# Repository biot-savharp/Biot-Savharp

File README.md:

# Biot-Savharp

Directory of folders/files in this repository
- ATTiny: Arduino code running on ATTiny45s (generating square waves sent to electromagnets to actuate strings)
- ArduinoISP: Arduino code to use an Arduino as an ISP to program ATTiny45s. This code is identical to the one found in the official Arduino Examples and requires some tweaking depending on what master Arduino is being used, etc.
- Datasheets: datasheets for the various chips used in the electromagnet driver board (AND gates, driver, and MOSFET)
- EM Harp: Eagle PCB layout files for the electromagnet driver board (.brd for board, .dru for design rules, .sch for schematic, and .epf for eagle project file)
- Keyboard: Arduino code running on an Arduino MEGA getting inputs from the keyboard and transmitting on/off signals for each key to the electromagnet driver board
- Keyboard_Laser: DWG file for laser-cutting the wooden keys of the keyboard
- MEGA Shield: Arduino MEGA breakout board interfacing with the keyboard and with connectors to the electromagnet driver board
- Notebook.pdf: my design notebook! The authoritative source of documentation, and a record of all the failures that led to eventual success
- harp_string_lengths.xlsx: an excel spreadsheet for calculating string lengths depending on tension

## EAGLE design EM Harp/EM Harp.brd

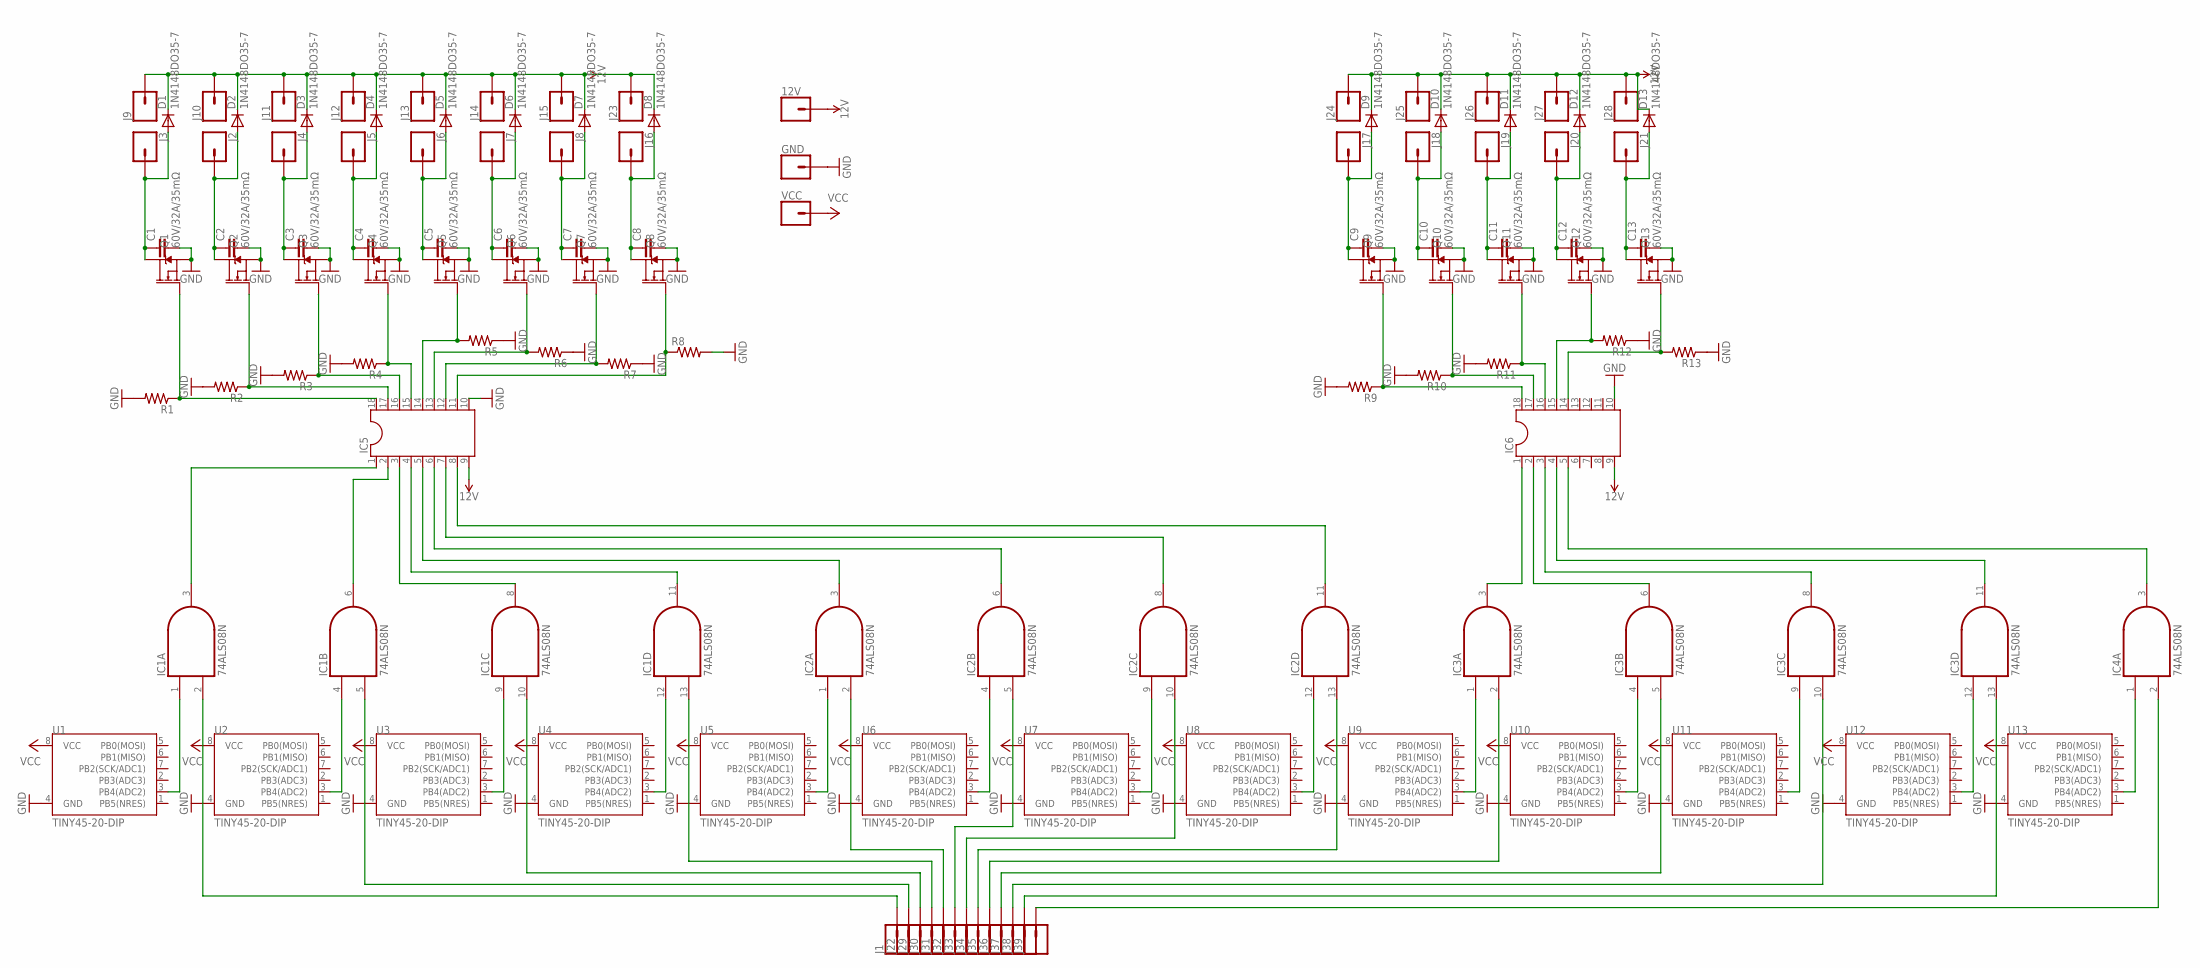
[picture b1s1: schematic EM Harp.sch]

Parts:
12V: CONN_01; 1X01
C1, C2, C3, C4, C5, C6, C7, C8, C9, C10, C11, C12, C13: C; C0805
D1, D2, D3, D4, D5, D6, D7, D8, D9, D10, D11, D12, D13: 1N4148DO35-7; DO35-7
GND: CONN_01; 1X01
IC1, IC2, IC3, IC4: 74ALS08N; DIL14
IC5, IC6: DIL18
J1, J2, J3, J4, J5, J6, J7, J8, J9, J10, J11, J12, J13, J14, J15, J16, J17, J18, J19, J20, J21, J22, J23, J24, J25, J26, J27, J28, J29, J30, J31, J32, J33, J34, J35, J36, J37, J38, J39: CONN_01; 1X01
Q1, Q2, Q3, Q4, Q5, Q6, Q7, Q8, Q9, Q10, Q11, Q12, Q13: 60V/32A/35mΩ; TO220V
R1: R-US_M0805; M0805
R2, R3, R4, R5, R6, R7, R8, R9, R10, R11, R12, R13: R-US_R0805; R0805
U1, U2, U3, U4, U5, U6, U7, U8, U9, U10, U11, U12, U13: TINY45-20-DIP; DIP08_MCU
VCC: CONN_01; 1X01

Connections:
12V: 12V.1, D1.C, D2.C, D3.C, D4.C, D5.C, D6.C, D7.C, D8.C, D9.C, D10.C, D11.C, D12.C, D13.C, IC5.9, IC6.9, J9.1, J10.1, J11.1, J12.1, J13.1, J14.1, J15.1, J23.1, J24.1, J25.1, J26.1, J27.1, J28.1
GND: C1.2, C2.2, C3.2, C4.2, C5.2, C6.2, C7.2, C8.2, C9.2, C10.2, C11.2, C12.2, C13.2, GND.1, IC1.7 (GND), IC2.7 (GND), IC3.7 (GND), IC4.7 (GND), IC5.10, IC6.10, Q1.3 (S), Q2.3 (S), Q3.3 (S), Q4.3 (S), Q5.3 (S), Q6.3 (S), Q7.3 (S), Q8.3 (S), Q9.3 (S), Q10.3 (S), Q11.3 (S), Q12.3 (S), Q13.3 (S), R1.2, R2.2, R3.2, R4.2, R5.1, R6.1, R7.1, R8.2, R9.2, R10.2, R11.2, R12.1, R13.1, U1.4 (GND), U2.4 (GND), U3.4 (GND), U4.4 (GND), U5.4 (GND), U6.4 (GND), U7.4 (GND), U8.4 (GND), U9.4 (GND), U10.4 (GND), U11.4 (GND), U12.4 (GND), U13.4 (GND)
unnamed: IC1.1 (I0), U1.3 (PB4(ADC2))
unnamed: IC1.4 (I0), U2.3 (PB4(ADC2))
unnamed: IC1.9 (I0), U3.3 (PB4(ADC2))
unnamed: IC1.12 (I0), U4.3 (PB4(ADC2))
unnamed: IC2.1 (I0), U5.3 (PB4(ADC2))
unnamed: IC2.4 (I0), U6.3 (PB4(ADC2))
unnamed: IC2.9 (I0), U7.3 (PB4(ADC2))
unnamed: IC2.12 (I0), U8.3 (PB4(ADC2))
unnamed: IC3.1 (I0), U9.3 (PB4(ADC2))
unnamed: IC3.4 (I0), U10.3 (PB4(ADC2))
unnamed: IC3.9 (I0), U11.3 (PB4(ADC2))
unnamed: IC3.12 (I0), U12.3 (PB4(ADC2))
unnamed: IC4.1 (I0), U13.3 (PB4(ADC2))
unnamed: IC1.2 (I1), J1.1
unnamed: IC1.5 (I1), J22.1
unnamed: IC1.10 (I1), J29.1
unnamed: IC1.13 (I1), J30.1
unnamed: IC2.2 (I1), J31.1
unnamed: IC2.5 (I1), J32.1
unnamed: IC2.10 (I1), J33.1
unnamed: IC2.13 (I1), J34.1
unnamed: IC3.2 (I1), J35.1
unnamed: IC3.5 (I1), J36.1
unnamed: IC3.10 (I1), J37.1
unnamed: IC3.13 (I1), J38.1
unnamed: IC4.2 (I1), J39.1
unnamed: IC1.3 (O), IC5.1
unnamed: IC1.6 (O), IC5.2
unnamed: IC1.8 (O), IC5.3
unnamed: IC1.11 (O), IC5.4
unnamed: IC2.3 (O), IC5.5
unnamed: IC2.6 (O), IC5.6
unnamed: IC2.8 (O), IC5.7
unnamed: IC2.11 (O), IC5.8
unnamed: IC3.3 (O), IC6.1
unnamed: IC3.6 (O), IC6.2
unnamed: IC3.8 (O), IC6.3
unnamed: IC3.11 (O), IC6.4
unnamed: IC4.3 (O), IC6.5
unnamed: IC5.18, Q1.1 (G), R1.1
unnamed: IC5.17, Q2.1 (G), R2.1
unnamed: IC5.16, Q3.1 (G), R3.1
unnamed: IC5.15, Q4.1 (G), R4.1
unnamed: IC5.14, Q5.1 (G), R5.2
unnamed: IC5.13, Q6.1 (G), R6.2
unnamed: IC5.12, Q7.1 (G), R7.2
unnamed: C1.1, D1.A, J3.1, Q1.2 (D)
unnamed: IC6.18, Q9.1 (G), R9.1
unnamed: IC6.17, Q10.1 (G), R10.1
unnamed: IC6.16, Q11.1 (G), R11.1
unnamed: IC6.15, Q12.1 (G), R12.2
unnamed: IC6.14, Q13.1 (G), R13.2
unnamed: C7.1, D7.A, J8.1, Q7.2 (D)
unnamed: C6.1, D6.A, J7.1, Q6.2 (D)
unnamed: C5.1, D5.A, J6.1, Q5.2 (D)
unnamed: C4.1, D4.A, J5.1, Q4.2 (D)
unnamed: C3.1, D3.A, J4.1, Q3.2 (D)
unnamed: C2.1, D2.A, J2.1, Q2.2 (D)
unnamed: C8.1, D8.A, J16.1, Q8.2 (D)
unnamed: C13.1, D13.A, J21.1, Q13.2 (D)
unnamed: C12.1, D12.A, J20.1, Q12.2 (D)
unnamed: C11.1, D11.A, J19.1, Q11.2 (D)
unnamed: C10.1, D10.A, J18.1, Q10.2 (D)
unnamed: C9.1, D9.A, J17.1, Q9.2 (D)
unnamed: IC5.11, Q8.1 (G), R8.1
VCC: IC1.14 (VCC), IC2.14 (VCC), IC3.14 (VCC), IC4.14 (VCC), U1.8 (VCC), U2.8 (VCC), U3.8 (VCC), U4.8 (VCC), U5.8 (VCC), U6.8 (VCC), U7.8 (VCC), U8.8 (VCC), U9.8 (VCC), U10.8 (VCC), U11.8 (VCC), U12.8 (VCC), U13.8 (VCC), VCC.1

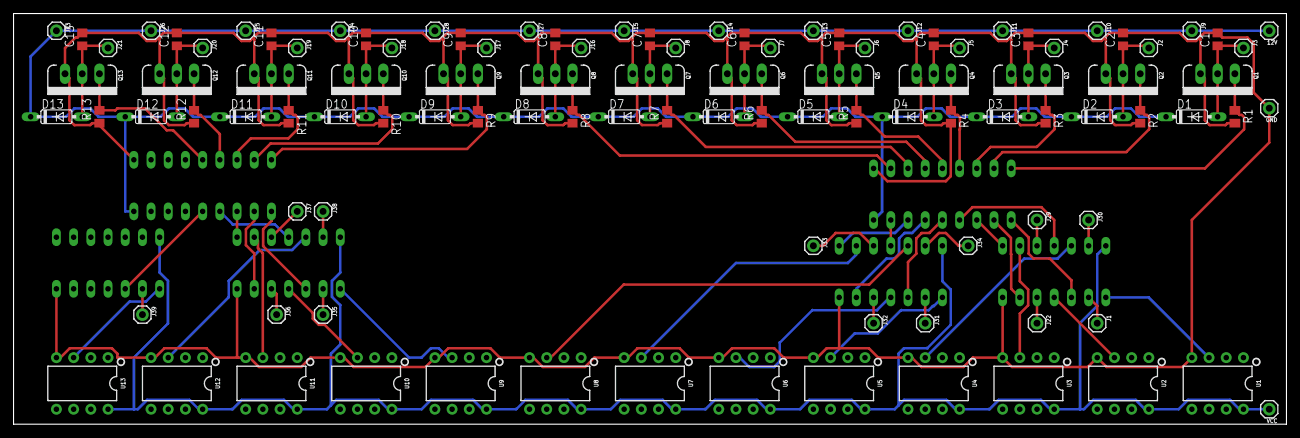
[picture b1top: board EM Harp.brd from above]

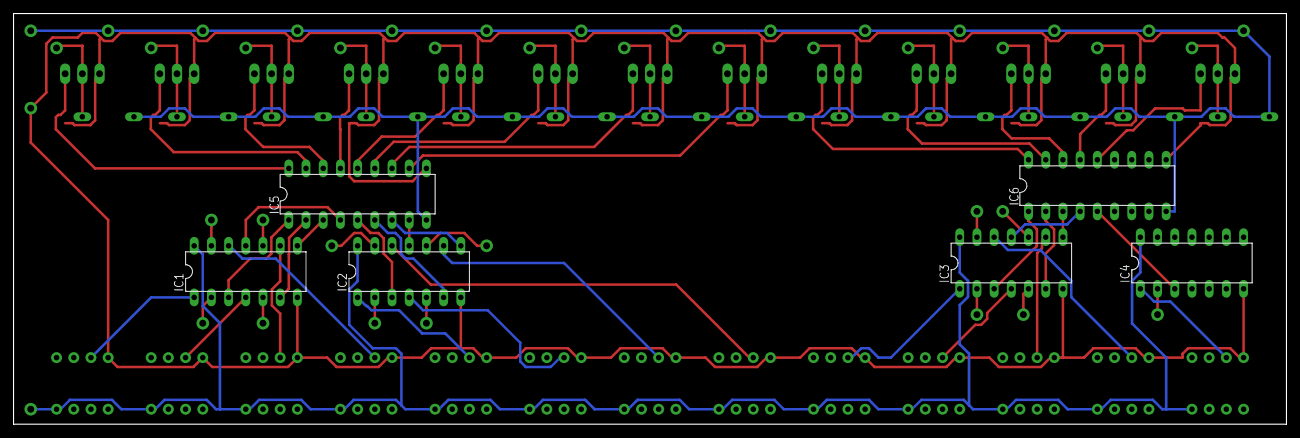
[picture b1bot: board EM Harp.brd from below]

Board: 2 copper layers, 187.9 x 60.6 mm, 113 parts (6 on the bottom side), 68 nets.

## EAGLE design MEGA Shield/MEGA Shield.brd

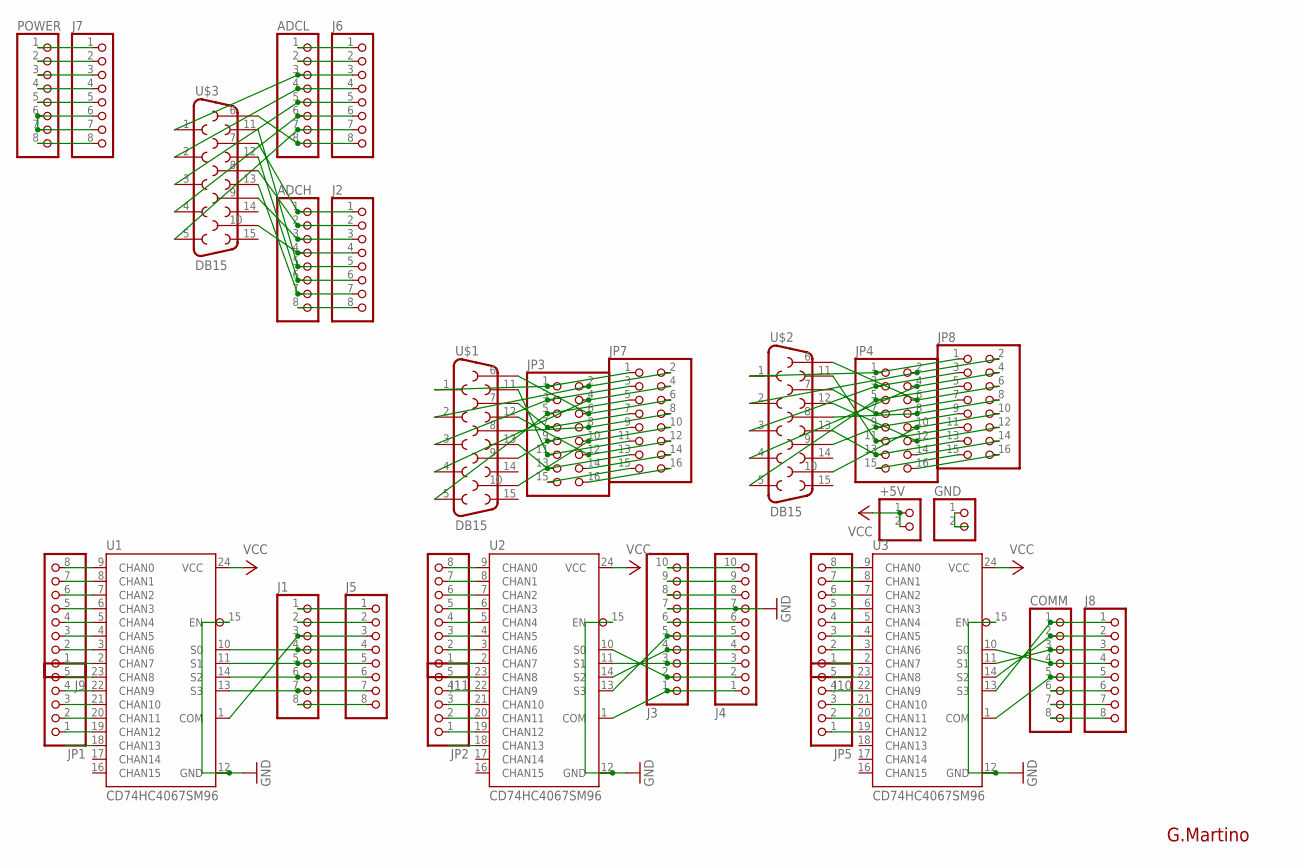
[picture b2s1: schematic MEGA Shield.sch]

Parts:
+5V: PINHD-1X2; 1X02
ADCH: PINHD-1X8TH; 1X08-TH
ADCL: PINHD-1X8TH; 1X08-TH
COMM: PINHD-1X8TH; 1X08-TH
GND: PINHD-1X2; 1X02
J1, J2, J5, J6, J7, J8, J9, J10, J11: PINHD-1X8TH; 1X08-TH
J3, J4: PINHD-1X10TH; 1X10-TH
JP1, JP2, JP5: PINHD-1X5; 1X05
JP3, JP4, JP7, JP8: PINHD-2X8; 2X08
POWER: PINHD-1X8TH; 1X08-TH
U1, U2, U3: CD74HC4067SM96; SSOP24
U$1, U$2, U$3: DB15

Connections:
+9V: J7.8, POWER.8
GND: J3.7, J4.7, U1.12 (GND), U1.15 (EN), U2.12 (GND), U2.15 (EN), U3.12 (GND), U3.15 (EN)
unnamed: GND.1, GND.2
unnamed: J3.1, J4.1, U2.1 (COM)
unnamed: J3.6, J4.6
unnamed: J7.5, POWER.5
unnamed: J3.4, J4.4, U2.14 (S2)
unnamed: J3.2, J4.2, U2.10 (S0)
unnamed: J3.3, J4.3, U2.11 (S1)
unnamed: J1.1, J5.1
unnamed: J1.2, J5.2
unnamed: J1.3, J5.3, U1.1 (COM)
unnamed: J1.4, J5.4, U1.10 (S0)
unnamed: J1.5, J5.5, U1.11 (S1)
unnamed: J1.6, J5.6, U1.14 (S2)
unnamed: J1.7, J5.7, U1.13 (S3)
unnamed: J1.8, J5.8
unnamed: J7.6, J7.7, POWER.6, POWER.7
unnamed: J9.8, U1.9 (CHAN0)
unnamed: ADCL.1, J6.1
unnamed: ADCL.2, J6.2
unnamed: ADCL.3, J6.3, U$3.1
unnamed: ADCL.4, J6.4, U$3.2
unnamed: ADCL.5, J6.5, U$3.3
unnamed: ADCL.6, J6.6, U$3.4
unnamed: J9.7, U1.8 (CHAN1)
unnamed: J9.6, U1.7 (CHAN2)
unnamed: J9.5, U1.6 (CHAN3)
unnamed: J9.4, U1.5 (CHAN4)
unnamed: J9.3, U1.4 (CHAN5)
unnamed: J9.2, U1.3 (CHAN6)
unnamed: J9.1, U1.2 (CHAN7)
unnamed: JP1.5, U1.23 (CHAN8)
unnamed: JP1.4, U1.22 (CHAN9)
unnamed: JP1.3, U1.21 (CHAN10)
unnamed: JP1.2, U1.20 (CHAN11)
unnamed: JP1.1, U1.19 (CHAN12)
unnamed: J10.8, U3.9 (CHAN0)
unnamed: ADCL.7, J6.7, U$3.5
unnamed: J10.7, U3.8 (CHAN1)
unnamed: J11.8, U2.9 (CHAN0)
unnamed: J11.7, U2.8 (CHAN1)
unnamed: J11.6, U2.7 (CHAN2)
unnamed: J11.5, U2.6 (CHAN3)
unnamed: J11.4, U2.5 (CHAN4)
unnamed: J11.3, U2.4 (CHAN5)
unnamed: J11.2, U2.3 (CHAN6)
unnamed: J11.1, U2.2 (CHAN7)
unnamed: JP2.5, U2.23 (CHAN8)
unnamed: JP2.4, U2.22 (CHAN9)
unnamed: JP2.3, U2.21 (CHAN10)
unnamed: JP2.2, U2.20 (CHAN11)
unnamed: JP2.1, U2.19 (CHAN12)
unnamed: J10.6, U3.7 (CHAN2)
unnamed: J10.5, U3.6 (CHAN3)
unnamed: J10.4, U3.5 (CHAN4)
unnamed: J10.3, U3.4 (CHAN5)
unnamed: J10.2, U3.3 (CHAN6)
unnamed: J10.1, U3.2 (CHAN7)
unnamed: JP5.5, U3.23 (CHAN8)
unnamed: JP5.4, U3.22 (CHAN9)
unnamed: JP5.3, U3.21 (CHAN10)
unnamed: ADCL.8, J6.8, U$3.6
unnamed: ADCH.1, J2.1, U$3.7
unnamed: JP5.2, U3.20 (CHAN11)
unnamed: JP5.1, U3.19 (CHAN12)
unnamed: ADCH.2, J2.2, U$3.8
unnamed: ADCH.3, J2.3, U$3.9
unnamed: ADCH.4, J2.4, U$3.10
unnamed: ADCH.5, J2.5, U$3.11
unnamed: ADCH.6, J2.6, U$3.12
unnamed: J7.4, POWER.4
unnamed: J3.9, J4.9
unnamed: ADCH.7, J2.7, U$3.13
unnamed: ADCH.8, J2.8
unnamed: COMM.1, J8.1, U3.13 (S3)
unnamed: COMM.2, J8.2, U3.14 (S2)
unnamed: COMM.3, J8.3, U3.11 (S1)
unnamed: COMM.4, J8.4, U3.10 (S0)
unnamed: COMM.5, J8.5, U3.1 (COM)
unnamed: COMM.6, J8.6
unnamed: COMM.7, J8.7
unnamed: COMM.8, J8.8
unnamed: J3.5, J4.5, U2.13 (S3)
unnamed: JP3.1, JP7.1, U$1.1
unnamed: JP3.2, JP7.2, U$1.2
unnamed: JP3.3, JP7.3, U$1.3
unnamed: JP3.4, JP7.4, U$1.4
unnamed: JP3.5, JP7.5, U$1.5
unnamed: JP3.6, JP7.6, U$1.6
unnamed: JP3.7, JP7.7, U$1.7
unnamed: JP3.8, JP7.8, U$1.8
unnamed: JP3.9, JP7.9, U$1.9
unnamed: JP3.10, JP7.10, U$1.10
unnamed: JP3.11, JP7.11, U$1.11
unnamed: JP3.12, JP7.12, U$1.12
unnamed: JP3.13, JP7.13, U$1.13
unnamed: JP3.14, JP7.14
unnamed: JP3.15, JP7.15
unnamed: JP3.16, JP7.16
unnamed: JP4.1, JP8.1, U$2.1
unnamed: JP4.2, JP8.2, U$2.2
unnamed: JP4.3, JP8.3, U$2.3
unnamed: JP4.4, JP8.4, U$2.4
unnamed: JP4.5, JP8.5, U$2.5
unnamed: JP4.6, JP8.6, U$2.6
unnamed: JP4.7, JP8.7, U$2.7
unnamed: JP4.8, JP8.8, U$2.8
unnamed: JP4.9, JP8.9, U$2.9
unnamed: JP4.10, JP8.10, U$2.10
unnamed: JP4.11, JP8.11, U$2.11
unnamed: JP4.12, JP8.12, U$2.12
unnamed: JP4.13, JP8.13, U$2.13
unnamed: JP4.14, JP8.14
unnamed: JP4.15, JP8.15
unnamed: JP4.16, JP8.16
unnamed: J7.2, POWER.2
unnamed: J7.1, POWER.1
unnamed: J3.8, J4.8
unnamed: J3.10, J4.10
RESET: J7.3, POWER.3
VCC: +5V.1, +5V.2, U1.24 (VCC), U2.24 (VCC), U3.24 (VCC)

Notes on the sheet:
G.Martino

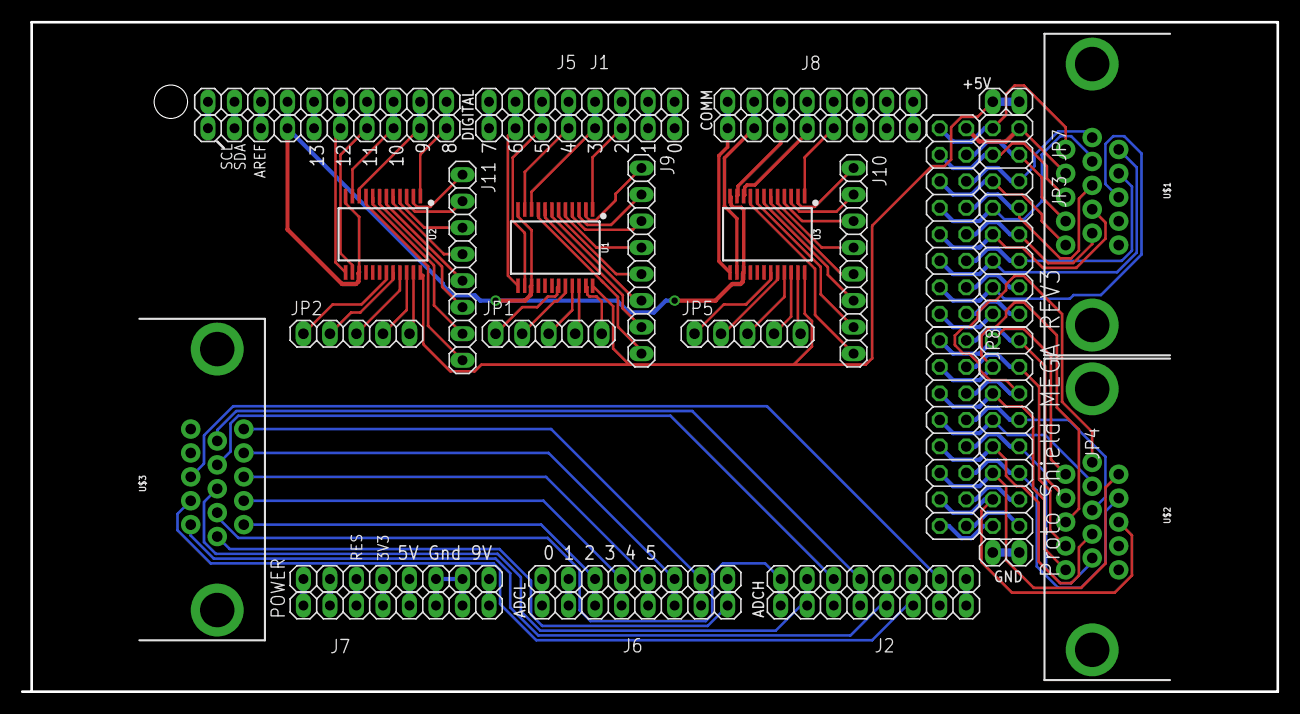
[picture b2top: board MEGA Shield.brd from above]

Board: 2 copper layers, 120.3 x 64.1 mm, 30 parts (0 on the bottom side), 122 nets.

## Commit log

2020-06-05 Add eagle files
2020-06-05 Add arduino code
2020-06-05 Add datasheets, keyboard laser dwg, and documentation notebook
2020-06-06 Describe repository contents

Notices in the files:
parts and their libraries:
SparkFun-Retired: Licensing: Creative Commons ShareAlike 4.0 International - https://creativecommons.org/licenses/by-sa/4.0
